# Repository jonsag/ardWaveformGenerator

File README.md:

# ardWaveformGenerator

Use an arduino as a waveform generator

## ardToneGenerator

[hackaday.io/project/12756-a-feature-rich-arduino-waveform-generator](hackaday.io/project/12756-a-feature-rich-arduino-waveform-generator)

## ardToneGeneratorJK

Basically same as above

## ardWaveFormGenerator

Uses an AD9833 programmable waveform generator.  

## ardWaveFormGenerator-AG

Uses an R2R DAC  

[https://www.instructables.com/Arduino-Waveform-Generator/](https://www.instructables.com/Arduino-Waveform-Generator/) by [amandaghassaei](https://www.instructables.com/member/amandaghassaei)

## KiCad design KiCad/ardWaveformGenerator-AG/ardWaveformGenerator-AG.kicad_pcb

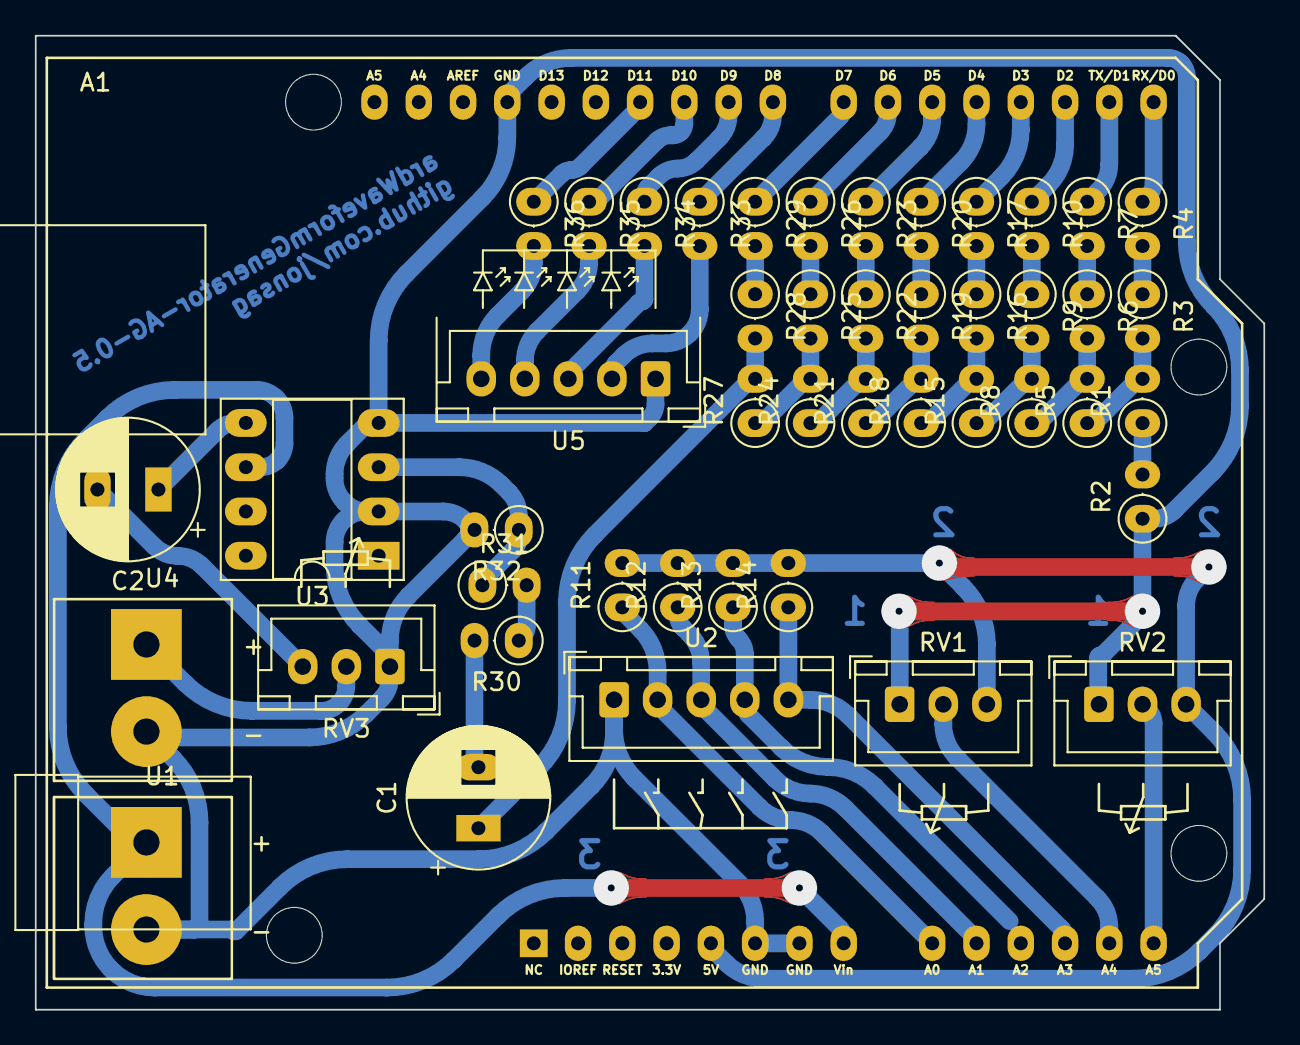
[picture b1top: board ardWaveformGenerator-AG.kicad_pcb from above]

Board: 2 copper layers, 70.5 x 55.9 mm, 47 parts (0 on the bottom side), 48 nets.

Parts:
A1: Arduino_UNO_R3; Arduino_UNO_R3_shield_large
C1, C2: 220u; CP_Radial_D8.0mm_P3.50mm_large
R1, R2, R3, R4, R5, R6, R7, R8, R9, R10, R11, R12, R13, R14, R15, R16, R17, R18, R19, R20, R21, R22, R23, R24, R25, R26, R27, R28, R29, R30, R31: 10k; R_Axial_DIN0207_L6.3mm_D2.5mm_P2.54mm_Vertical_large
R32: 2.2k; R_Axial_DIN0207_L6.3mm_D2.5mm_P2.54mm_Vertical_large
R33, R34, R35, R36: 220R; R_Axial_DIN0207_L6.3mm_D2.5mm_P2.54mm_Vertical_large
RV1, RV2, RV3: 10k; 3-pin JST Potentiometer
U1: Power in; 2-pole_power_in_screw_terminal
U2: 5-pin_4_buttons_+_common; 5-pin JST 4 buttons + common
U3: LM386; DIP-8_W7.62mm_Socket_w_dip_packet_LongPads
U4: Output; 2-pole_power_in_screw_terminal
U5: 5-pin_4_LED_header; 5-pin JST 4-LED

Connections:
+5V: A1.5 (+5V), R11.2, R12.2, R13.2, R14.2, RV1.3, RV2.3
A0: A1.9 (A0), R11.1, U2.2 (But1)
A1: A1.10 (A1), R12.1, U2.3 (But2)
A2: A1.11 (A2), R13.1, U2.4 (But3)
A3: A1.12 (A3), R14.1, U2.5 (But4)
A4: A1.13 (SDA/A4), RV1.2
A5: A1.14 (SCL/A5), RV2.2
D0: A1.15 (D0/RX), R4.1
D1: A1.16 (D1/TX), R7.1
D2: A1.17 (D2), R10.1
D3: A1.18 (D3), R17.1
D4: A1.19 (D4), R20.1
D5: A1.20 (D5), R23.1
D6: A1.21 (D6), R26.1
D7: A1.22 (D7), R29.1
D8: A1.23 (D8), R33.1
D9: A1.24 (D9), R34.1
D10: A1.25 (D10), R35.1
D11: A1.26 (D11), R36.1
GND: A1.6 (GND), A1.7 (GND), A1.29 (GND), R2.1, R32.2, RV1.1, RV2.1, RV3.1, U1.2 (-), U2.1 (Com), U3.2 (-), U3.4 (GND), U4.2 (-), U5.1 (GND)
unnamed: C1.1, R27.2, R28.2
unnamed: C1.2, R30.2
unnamed: C2.1, U3.5
unnamed: C2.2, RV3.3
unnamed: R33.2, U5.2
unnamed: R34.2, U5.3
unnamed: R35.2, U5.4
unnamed: R36.2, U5.5
unnamed: R1.1, R2.2
unnamed: R1.2, R3.2, R5.1
unnamed: R3.1, R4.2
unnamed: R5.2, R6.2, R8.1
unnamed: R6.1, R7.2
unnamed: R9.1, R10.2
unnamed: R8.2, R9.2, R15.1
unnamed: R15.2, R16.2, R18.1
unnamed: R16.1, R17.2
unnamed: R18.2, R19.2, R21.1
unnamed: R19.1, R20.2
unnamed: R21.2, R22.2, R24.1
unnamed: R22.1, R23.2
unnamed: R24.2, R25.2, R27.1
unnamed: R25.1, R26.2
unnamed: R28.1, R29.2
unnamed: R30.1, R31.2
unnamed: R31.1, R32.1, U3.3 (+)
unnamed: RV3.2, U4.1 (+)
VCC: A1.8 (VIN), U1.1 (+), U3.6 (V+)

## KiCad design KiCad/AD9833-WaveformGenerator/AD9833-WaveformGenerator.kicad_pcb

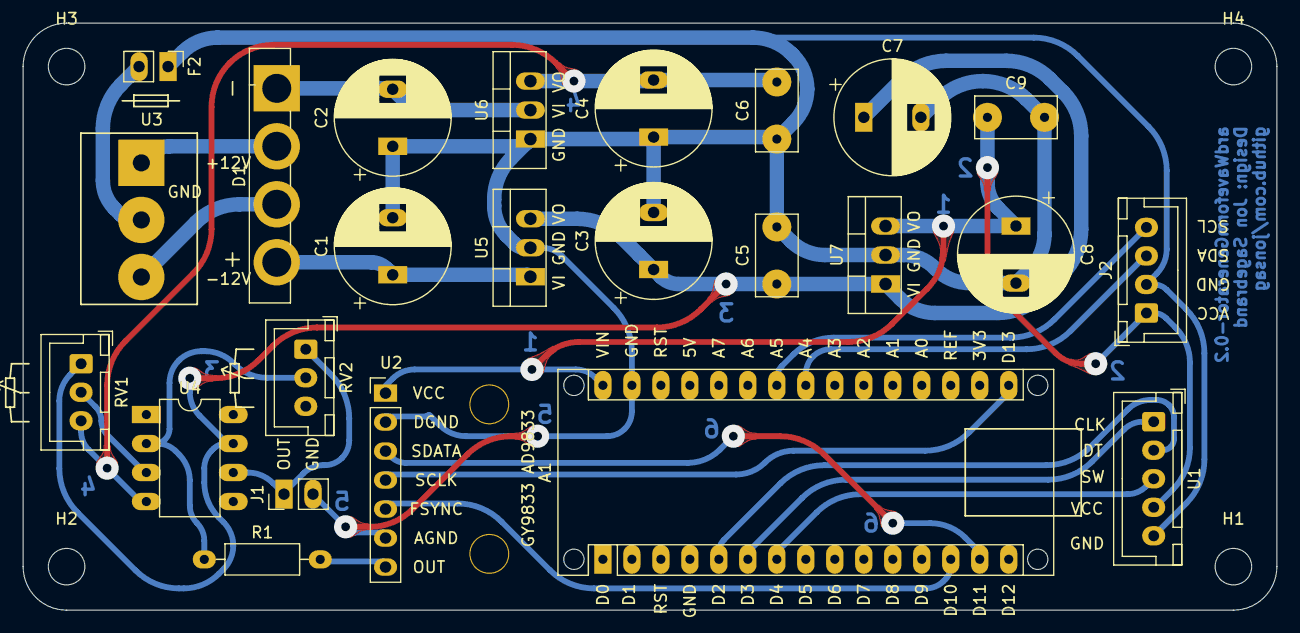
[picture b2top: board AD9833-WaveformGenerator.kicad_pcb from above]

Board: 2 copper layers, 109.9 x 51.4 mm, 28 parts (0 on the bottom side), 21 nets.

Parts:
A1: Arduino_Nano_v3.x; Arduino_Nano_WithMountingHoles_larger
C1, C2, C3, C4, C7, C8: 1000u; CP_Radial_D10.0mm_P5.00mm_larger
C5, C6, C9: 100n; C_Rect_L7.0mm_W3.5mm_P5.00mm_larger
D1: B40C2300-1500A; GBU-806
F2: Fuse; 2-pin_Fuse_header_large
H1, H2, H3, H4: MountingHole; MountingHole_3.2mm_M3
J1: Conn_Coaxial; 2-pin_Output_header_large
J2: 4-pin_I2C_LCD_header; 4-pin JST LCD
R1: 2.2k; R_Axial_DIN0207_L6.3mm_D2.5mm_P10.16mm_Horizontal_large
RV1: 10k; 3-pin JST Potentiometer
RV2: 50k; 3-pin JST Potentiometer
U1: KY-040_Rotary_Encoder; 5-pin JST Rotary Encoder
U2: GY-9833_AD9833; GY-9833_AD9833_w_header_large
U3: 3-pole_Power_input_screw_terminal; 3-pole_screw_terminal_+12V,-12V_input
U4: TL071; DIP-8_W7.62mm_large
U5: LM7812_TO220; LM7812_TO-220-3_Vertical_larger
U6: LM7912_TO220; LM7912_TO-220-3_Vertical_larger
U7: LM7805_TO220; LM7805_TO-220-3_Vertical_larger

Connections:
+5V: A1.30 (VIN), C8.1, C9.1, J2.1 (+5V), U1.4 (VCC), U2.1 (VCC), U7.3 (VO)
+12V: C3.1, C5.1, C7.1, RV1.1, U4.7 (V+), U5.3 (VO), U7.1 (VI)
-12V: C4.2, C6.2, RV1.3, U4.4 (V-), U6.3 (VO)
GND: A1.29 (GND), C1.2, C2.1, C3.2, C4.1, C5.2, C6.1, C7.2, C8.2, C9.2, F2.1, J1.2 (Ext), J2.2 (GND), U1.5 (GND), U2.2 (DGND), U2.6 (AGND), U5.2 (GND), U6.1 (GND), U7.2 (GND)
unnamed: A1.5 (D2), U1.2 (DT)
unnamed: A1.6 (D3), U1.1 (CLK)
unnamed: A1.7 (D4), U1.3 (SW)
unnamed: A1.13 (D10), U2.5 (FSYNC)
unnamed: A1.14 (D11), U2.3 (SDATA)
unnamed: A1.16 (D13), U2.4 (SCLK)
unnamed: A1.23 (A4), J2.3 (SDA)
unnamed: A1.24 (A5), J2.4 (SCL)
unnamed: C2.2, D1.1 (-), U6.2 (VI)
unnamed: D1.2, U3.1 (+12V)
unnamed: D1.3, U3.3 (-12V)
unnamed: C1.1, D1.4 (+), U5.1 (VI)
unnamed: F2.2, U3.2 (GND)
unnamed: J1.1 (In), RV2.1, U4.6
unnamed: R1.1, RV2.2, U4.2 (-)
unnamed: R1.2, U2.7 (OUT)
unnamed: RV1.2, U4.3 (+)

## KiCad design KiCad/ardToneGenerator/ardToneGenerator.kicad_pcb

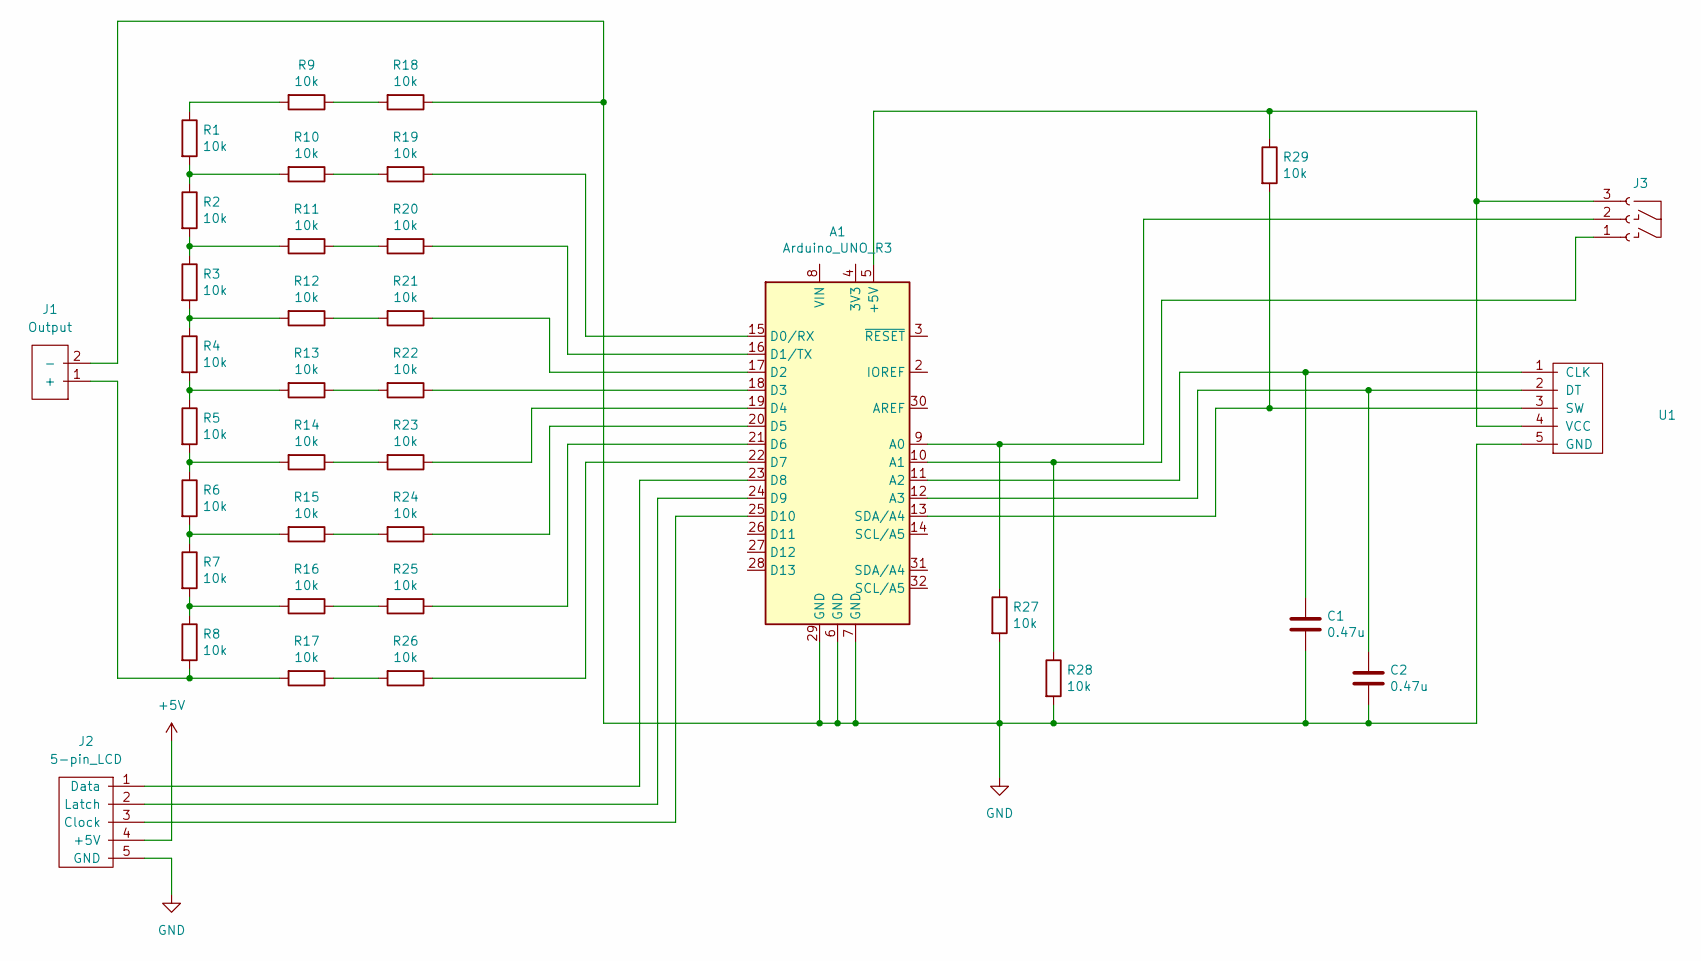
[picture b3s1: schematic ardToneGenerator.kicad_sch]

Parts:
A1: Arduino_UNO_R3; Arduino_UNO_R3_shield_large
C1, C2: 0.47u; C_Disc_D3.0mm_W1.6mm_P2.50mm_larg
J1: Output; 2-pin_Output_header_large
J2: 5-pin_LCD; 5-pin JST LiquidCrystal595
J3: 3-pin_2-buttons; 3-pin JST 2-buttons
R1, R2, R3, R4, R5, R6, R7, R8, R9, R10, R11, R12, R13, R14, R15, R16, R17, R18, R19, R20, R21, R22, R23, R24, R25, R26, R27, R28, R29: 10k; R_Axial_DIN0207_L6.3mm_D2.5mm_P10.16mm_Horizontal_large
U1: KY-040_Rotary_Encoder; 5-pin JST Rotary Encoder

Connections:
+5V: J2.4 (+5V)
GND: A1.6 (GND), A1.7 (GND), A1.29 (GND), C1.2, C2.2, J1.2 (-), J2.5 (GND), R18.1, R27.2, R28.2, U1.5 (GND)
unnamed: A1.5 (+5V), J3.3 (Sig), R29.1, U1.4 (VCC)
unnamed: A1.10 (A1), J3.1 (+), R28.1
unnamed: A1.11 (A2), C1.1, U1.1 (CLK)
unnamed: A1.12 (A3), C2.1, U1.2 (DT)
unnamed: A1.13 (SDA/A4), R29.2, U1.3 (SW)
unnamed: A1.15 (D0/RX), R19.1
unnamed: A1.16 (D1/TX), R20.1
unnamed: A1.17 (D2), R21.1
unnamed: A1.18 (D3), R22.1
unnamed: A1.19 (D4), R23.1
unnamed: A1.20 (D5), R24.1
unnamed: A1.21 (D6), R25.1
unnamed: A1.22 (D7), R26.1
unnamed: A1.23 (D8), J2.1 (Data)
unnamed: A1.24 (D9), J2.2 (Latch)
unnamed: A1.25 (D10), J2.3 (Clock)
unnamed: R1.1, R9.2
unnamed: R1.2, R2.1, R10.2
unnamed: R10.1, R19.2
unnamed: R11.1, R20.2
unnamed: R2.2, R3.1, R11.2
unnamed: R12.1, R21.2
unnamed: R3.2, R4.1, R12.2
unnamed: R13.1, R22.2
unnamed: R4.2, R5.1, R13.2
unnamed: R14.1, R23.2
unnamed: R5.2, R6.1, R14.2
unnamed: R15.1, R24.2
unnamed: R6.2, R7.1, R15.2
unnamed: R16.1, R25.2
unnamed: R7.2, R8.1, R16.2
unnamed: R17.1, R26.2
unnamed: J1.1 (+), R8.2, R17.2
unnamed: R9.1, R18.2
unnamed: A1.9 (A0), J3.2 (Sig), R27.1

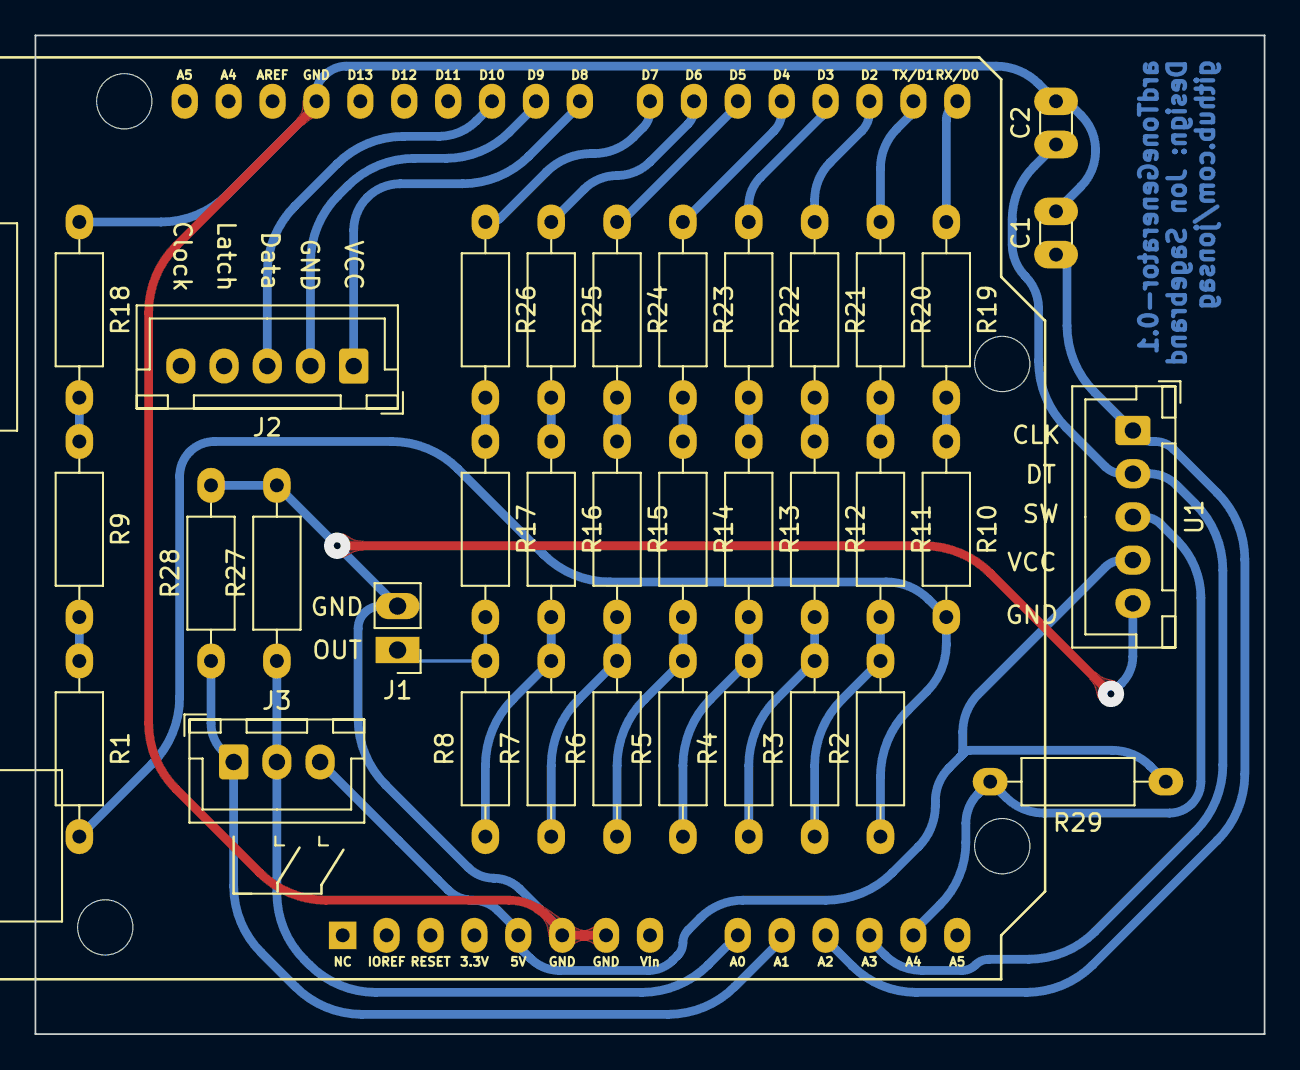
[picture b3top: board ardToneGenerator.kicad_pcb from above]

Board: 2 copper layers, 71.1 x 57.8 mm, 36 parts (0 on the bottom side), 36 nets.

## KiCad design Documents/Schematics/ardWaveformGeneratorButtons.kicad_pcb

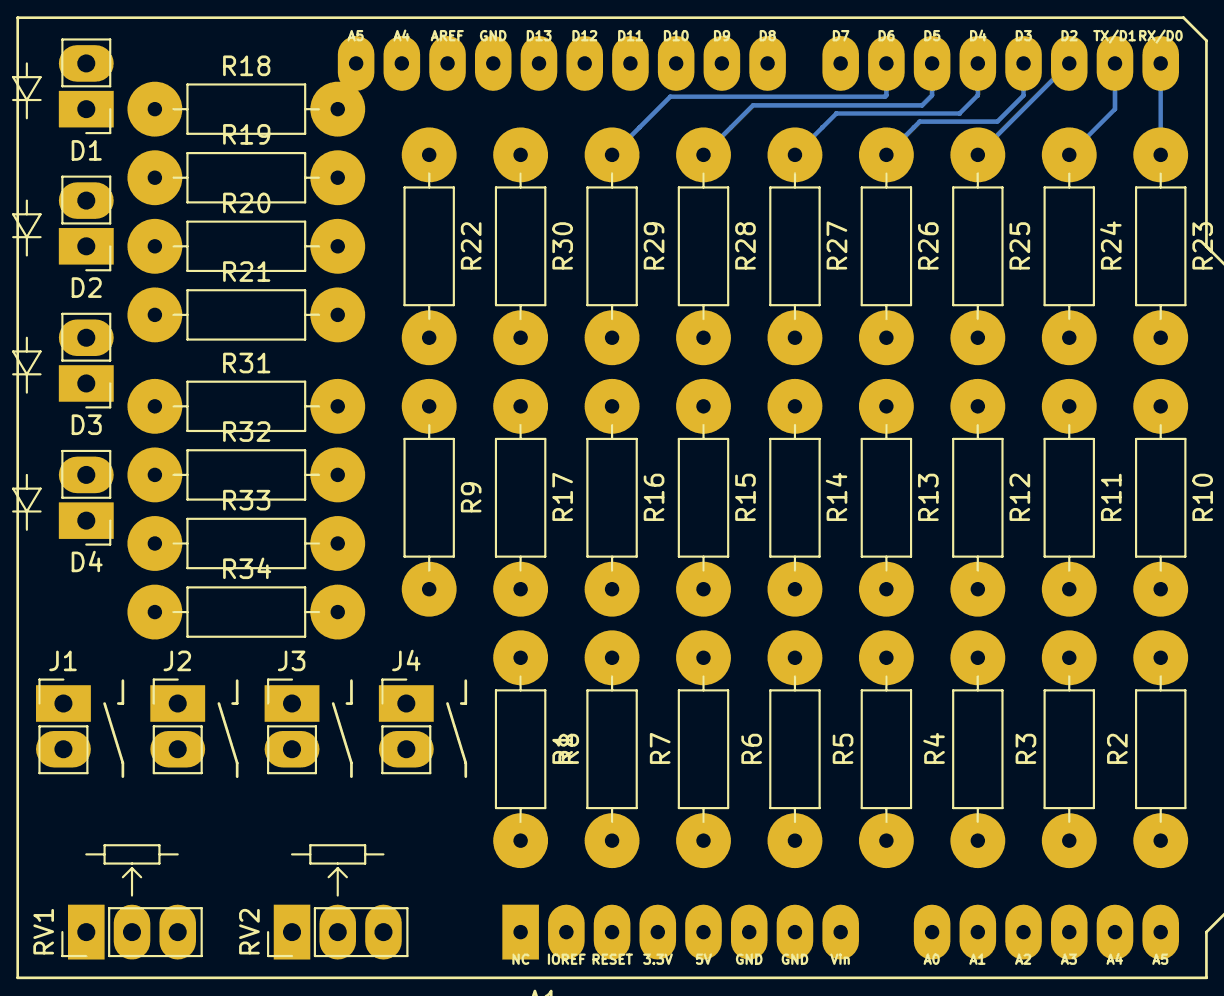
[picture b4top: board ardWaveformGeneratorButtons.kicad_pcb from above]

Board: 2 copper layers, 45 parts (0 on the bottom side), 43 nets.

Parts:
A1: Arduino_UNO_R3; Arduino_UNO_R3_shield_larger_pads
D1, D2, D3, D4: LED; 2-pin_LED_header_large
J1, J2, J3, J4: 2-pin_NO_switch_header; 2-pin_NO_switch_header_larger_pads
R1, R2, R3, R4, R5, R6, R7, R8, R9, R10, R11, R12, R13, R14, R15, R16, R17, R22, R23, R24, R25, R26, R27, R28, R29, R30, R31, R32, R33, R34: 10k; R_Axial_DIN0207_L6.3mm_D2.5mm_P10.16mm_Horizontal_larger_pa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
R18, R19, R20, R21: 330R; R_Axial_DIN0207_L6.3mm_D2.5mm_P10.16mm_Horizontal_larger_pa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
RV1, RV2: 10k; 3-pin_potentiometer_header_larger_pads

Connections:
unnamed: A1.5, R31.2, R32.2, R33.2, R34.2, RV1.1, RV2.1
unnamed: A1.7, J1.1, J2.1, J3.1, J4.1, RV1.3, RV2.3
unnamed: A1.9, J1.2, R31.1
unnamed: A1.10, J2.2, R32.1
unnamed: A1.11, J3.2, R33.1
unnamed: A1.12, J4.2, R34.1
unnamed: A1.13, RV1.2
unnamed: A1.14, RV2.2
unnamed: A1.15, R23.1
unnamed: A1.16, R24.1
unnamed: A1.17, R25.1
unnamed: A1.18, R26.1
unnamed: A1.19, R27.1
unnamed: A1.20, R28.1
unnamed: A1.21, R29.1
unnamed: A1.22, R30.1
unnamed: A1.23, D1.2
unnamed: A1.24, D2.2
unnamed: A1.25, D3.2
unnamed: A1.26, D4.2
unnamed: D1.1, R18.1
unnamed: D2.1, R19.1
unnamed: D3.1, R20.1
unnamed: D4.1, R21.1
unnamed: R1.1, R9.2
unnamed: R1.2, R2.1, R10.2
unnamed: R10.1, R23.2
unnamed: R11.1, R24.2
unnamed: R2.2, R3.1, R11.2
unnamed: R12.1, R25.2
unnamed: R3.2, R4.1, R12.2
unnamed: R13.1, R26.2
unnamed: R4.2, R5.1, R13.2
unnamed: R14.1, R27.2
unnamed: R5.2, R6.1, R14.2
unnamed: R15.1, R28.2
unnamed: R6.2, R7.1, R15.2
unnamed: R16.1, R29.2
unnamed: R7.2, R8.1, R16.2
unnamed: R17.1, R30.2
unnamed: R9.1, R22.2
Out+: R8.2, R17.2
Out-: A1.29, R18.2, R19.2, R20.2, R21.2, R22.1

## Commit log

2020-04-13 first schematics based on amandaghassaei
2020-04-13 first sketch from amandaghassaei
2020-04-13 sketch from joekutz
2020-04-18 sketch work
2020-04-18 now prints to LCD
2020-04-18 deleted sketch
2020-04-18 added schematics
2020-04-18 update sketch
2020-04-18 cleanup and comments in sketch
2020-04-19 sketch now works fine
2020-04-22 renamed joe kutz's
2020-04-22 uploaded sketch that uses buttons
2020-05-01 started on new WFG
2020-05-01 new sketch
2020-05-01 added case stl
2020-05-02 Schematics
2020-05-02 kicad pcb
2020-05-04 new pcb layout
2022-09-10 deletions
2022-09-10 kicad6
2022-09-11 AG arduino
2022-09-11 AG pio
2022-09-11 pio fir AD9833 variant
2022-10-24 ardWaveformGenerator-0.2
2022-10-24 ardToneGenerator converted to pio
2022-10-24 ardToneGenerator-0.1
2022-10-25 ardWaveformGenerator-AG-pio with pcb-0.2
2022-10-25 LED-header on pcb, version 0.3
2022-10-26 new buttons
2022-10-28 VeroRoute and AG v0.4
2022-10-28 complete veroroute
2022-10-29 wider tracks v0.5
2025-02-02 revisions and an new project added
2025-02-02 deleted unnecessary file
